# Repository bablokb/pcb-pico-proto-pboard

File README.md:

Protoyping Board for the Raspberry Pi Pico
==========================================

This is a small prototyping board for the Pico. Besides
the normal 2x20 through holes for the Pico, the PCB also
provides additional sockets for the connection of peripherals.

The idea of this board is to simplify software-development
for standard breakouts, because it provides sockets for
these components and thus no wiring is necessary.

Some supported components:

  - Mini-I2C-OLED
  - EYESPI (typically for SPI-displays)
  - 2x Grove (I2C0/UART0 and I2C1)
  - ESP-01S or Lilygo T-01 C3
  - passive buzzer
  - MAX98357A (I2S mono-amplifier)
  - button-breakout (3xbutton, 1xGND)
  - RTC-socket (for this PCB: <https://github.com/bablokb/pcb-pico-pcf8563.git>)
  - Adafruit TPL5110 power-switch breakout
  - SD-card socket (on-board)
  - JST-PH2 battery connector
  - JST-PH3 connector (ADC)

Note that some components share pins, so it is *not possible* to use
all components in parallel! See [pinout](./pins.md) for details.

Ready to use Gerber, BOM and POS files for JLCPCB are in the subdirectory
"production_files".

Schematic
---------

Layout
------

3D-Views
--------

License
-------

[![CC BY-SA 4.0][cc-by-sa-shield]][cc-by-sa]

This work is licensed under a
[Creative Commons Attribution-ShareAlike 4.0 International
License][cc-by-sa].

[![CC BY-SA 4.0][cc-by-sa-image]][cc-by-sa]

[cc-by-sa]: http://creativecommons.org/licenses/by-sa/4.0/
[cc-by-sa-image]: https://licensebuttons.net/l/by-sa/4.0/88x31.png
[cc-by-sa-shield]:
https://img.shields.io/badge/License-CC%20BY--SA%204.0-lightgrey.svg

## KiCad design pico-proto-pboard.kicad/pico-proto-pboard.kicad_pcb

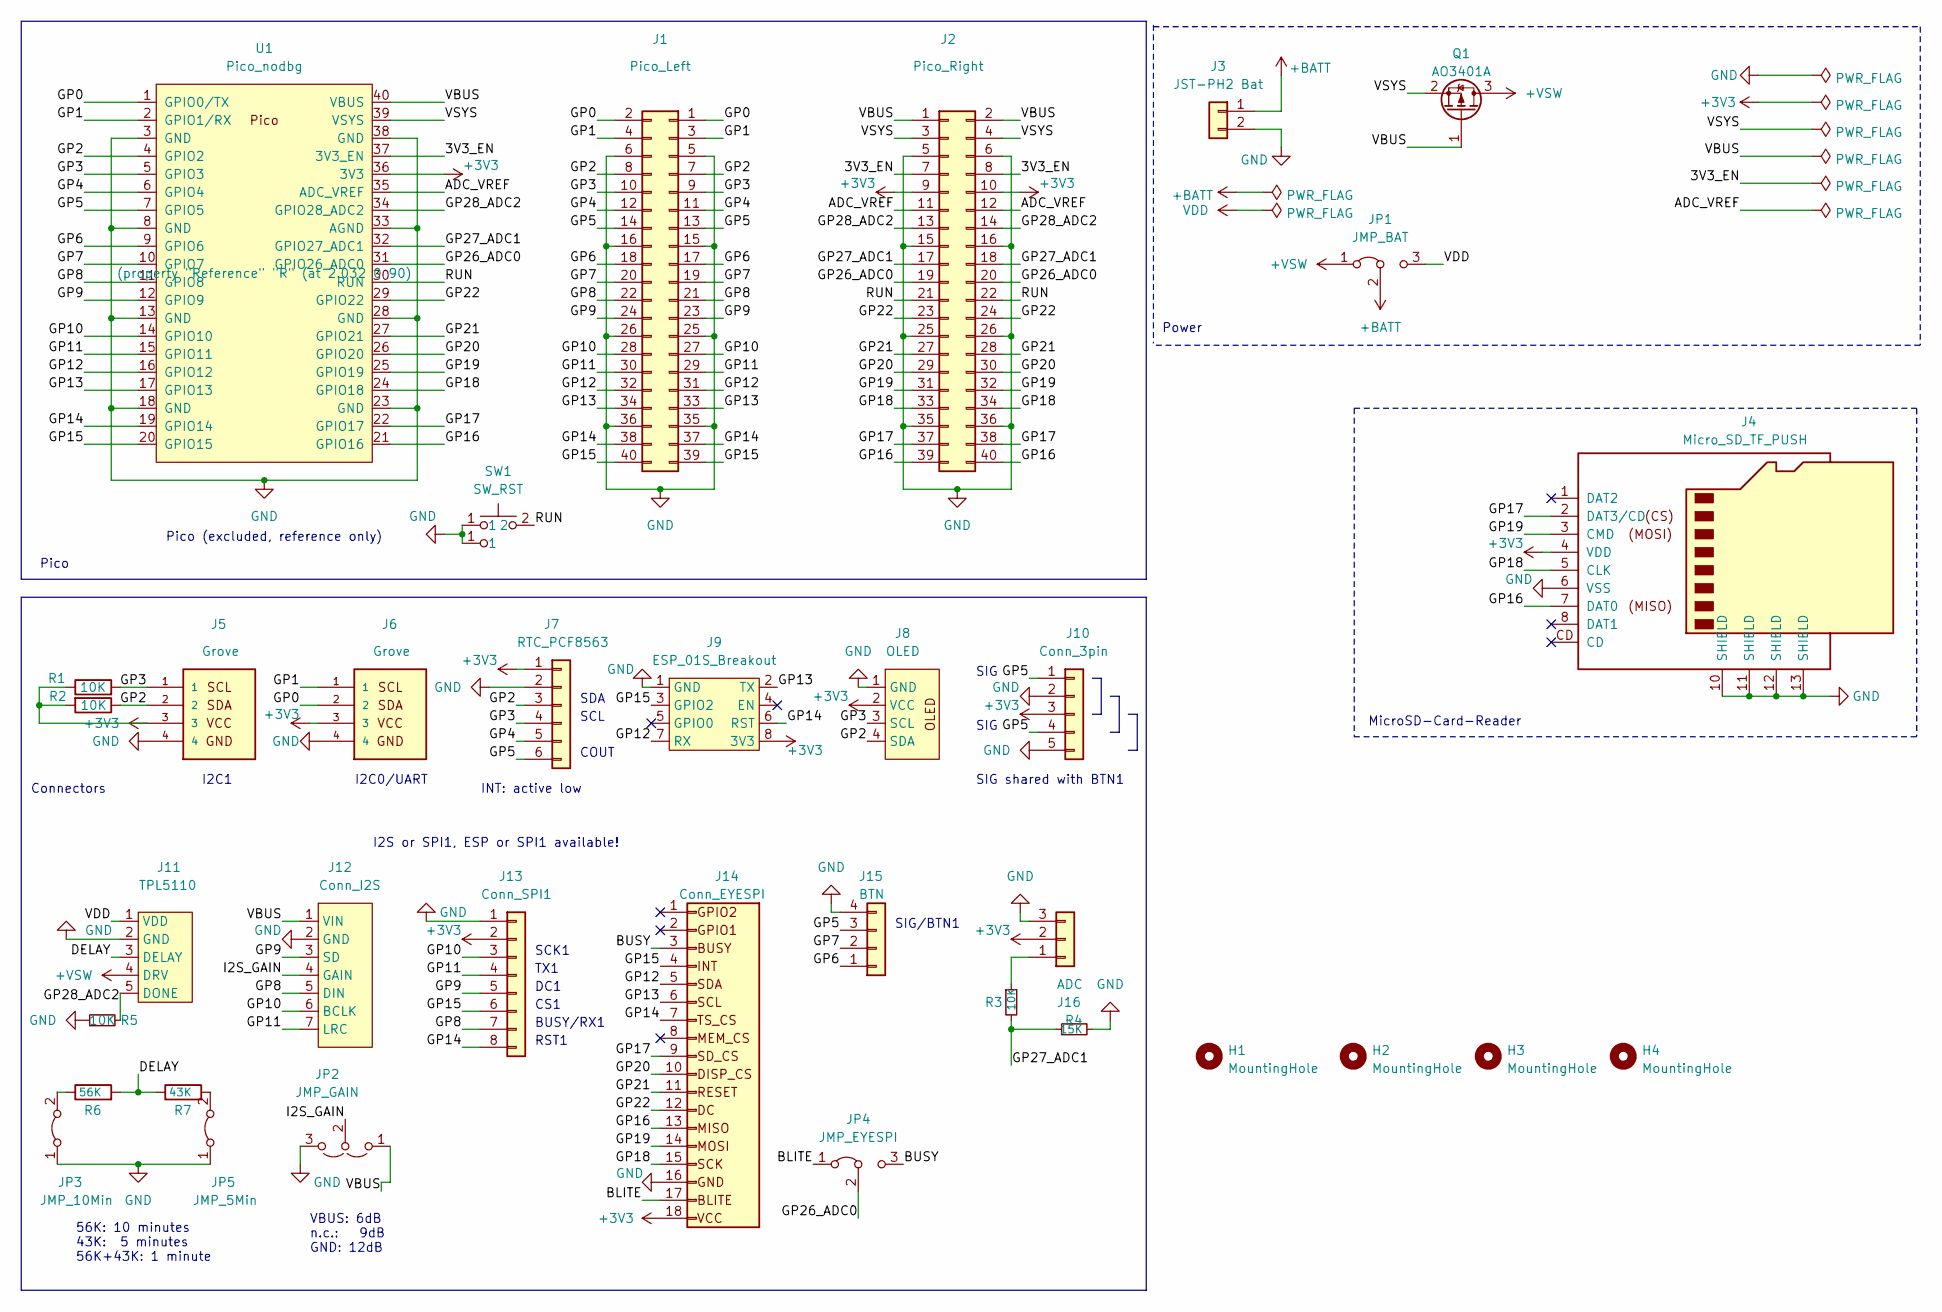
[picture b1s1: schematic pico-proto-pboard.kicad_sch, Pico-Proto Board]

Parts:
H1, H2, H3, H4: MountingHole; MountingHole_2.5mm
J1: Pico_Left; PinSocket_2x20_P2.54mm_Vertical
J2: Pico_Right; PinSocket_2x20_P2.54mm_Vertical
J3: JST-PH2 Bat; JST_PH_S2B-PH-SM4-TB_1x02-1MP_P2.00mm_Horizontal; LCSC C295747
J4: Micro_SD_TF_PUSH; TF-Push; LCSC C393941
J5, J6: Grove; grove_vertical
J7: RTC_PCF8563; PinSocket_1x06_P2.54mm_Vertical
J8: OLED; OLED_Display
J9: ESP_01S_Breakout
J10: Conn_3pin; PinSocket_1x05_P2.54mm_Vertical
J11: TPL5110; TPL5110_Breakout
J12: Conn_I2S; MAX98357A_Breakout
J13: Conn_SPI1; PinHeader_2x04_P2.54mm_Vertical
J14: Conn_EYESPI; G-Shell-FPC_1x18_P0.50mm_Horizontal; LCSC C21260844
J15: BTN; PinSocket_1x04_P2.54mm_Vertical
J16: ADC; JST_PH_S3B-PH-SM4-TB_1x03-1MP_P2.00mm_Horizontal
JP1: JMP_BAT; PinHeader_1x03_P2.54mm_Vertical
JP2: JMP_GAIN; PinHeader_1x03_P2.54mm_Vertical
JP3: JMP_10Min; SolderJumper-2_P1.3mm_Bridged_Pad1.0x1.5mm
JP4: JMP_EYESPI; SolderJumper-3_P1.3mm_Bridged12_Pad1.0x1.5mm
JP5: JMP_5Min; SolderJumper-2_P1.3mm_Bridged_Pad1.0x1.5mm
Q1: AO3401A; SOT-23; LCSC C15127
R1, R2, R3, R5: 10K; R_0402_1005Metric; LCSC C25744
R4: 15K; R_0402_1005Metric; LCSC C25756
R6: 56K; R_0402_1005Metric; LCSC C25796
R7: 43K; R_0603_1608Metric; LCSC C23172
SW1: SW_RST; SW_PUSH_SLIM_1x4
U1: Pico_nodbg; RPi_Pico_SMD_TH_nodbg; LCSC (property "Reference" "R" (at 2.032 0 9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

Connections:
+3V3: J2.9, J2.10, J4.4 (VDD), J5.3, J6.3, J7.1, J8.2 (VCC), J9.8 (3V3), J10.3, J13.2, J14.18, J16.2, R1.1, R2.2, U1.36 (3V3)
+BATT: J3.1, JP1.2 (C)
+VSW: J11.4 (DRV), JP1.1 (A), Q1.3 (D)
/3V3_EN: J2.7, J2.8, U1.37 (3V3_EN)
/ADC_VREF: J2.11, J2.12, U1.35 (ADC_VREF)
/BLITE: J14.17, JP4.1 (A)
/BUSY: J14.3, JP4.3 (B)
/DELAY: J11.3 (DELAY), R6.2, R7.1
/GP0: J1.1, J1.2, J6.2, U1.1 (GPIO0/TX)
/GP1: J1.3, J1.4, J6.1, U1.2 (GPIO1/RX)
/GP2: J1.7, J1.8, J5.2, J7.3, J8.4 (SDA), R2.1, U1.4 (GPIO2)
/GP3: J1.9, J1.10, J5.1, J7.4, J8.3 (SCL), R1.2, U1.5 (GPIO3)
/GP4: J1.11, J1.12, J7.5, U1.6 (GPIO4)
/GP5: J1.13, J1.14, J7.6, J10.1, J10.4, J15.3, U1.7 (GPIO5)
/GP6: J1.17, J1.18, J15.1, U1.9 (GPIO6)
/GP7: J1.19, J1.20, J15.2, U1.10 (GPIO7)
/GP8: J1.21, J1.22, J12.5 (DIN), J13.7, U1.11 (GPIO8)
/GP9: J1.23, J1.24, J12.3 (SD), J13.5, U1.12 (GPIO9)
/GP10: J1.27, J1.28, J12.6 (BCLK), J13.3, U1.14 (GPIO10)
/GP11: J1.29, J1.30, J12.7 (LRC), J13.4, U1.15 (GPIO11)
/GP12: J1.31, J1.32, J9.7 (RX), J14.5, U1.16 (GPIO12)
/GP13: J1.33, J1.34, J9.2 (TX), J14.6, U1.17 (GPIO13)
/GP14: J1.37, J1.38, J9.6 (RST), J13.8, J14.7, U1.19 (GPIO14)
/GP15: J1.39, J1.40, J9.3 (GPIO2), J13.6, J14.4, U1.20 (GPIO15)
/GP16: J2.39, J2.40, J4.7 (DAT0), J14.13, U1.21 (GPIO16)
/GP17: J2.37, J2.38, J4.2 (DAT3/CD), J14.9, U1.22 (GPIO17)
/GP18: J2.33, J2.34, J4.5 (CLK), J14.15, U1.24 (GPIO18)
/GP19: J2.31, J2.32, J4.3 (CMD), J14.14, U1.25 (GPIO19)
/GP20: J2.29, J2.30, J14.10, U1.26 (GPIO20)
/GP21: J2.27, J2.28, J14.11, U1.27 (GPIO21)
/GP22: J2.23, J2.24, J14.12, U1.29 (GPIO22)
/GP26_ADC0: J2.19, J2.20, JP4.2 (C), U1.31 (GPIO26_ADC0)
/GP27_ADC1: J2.17, J2.18, R3.2, R4.1, U1.32 (GPIO27_ADC1)
/GP28_ADC2: J2.13, J2.14, J11.5 (DONE), R5.2, U1.34 (GPIO28_ADC2)
/I2S_GAIN: J12.4 (GAIN), JP2.2 (C)
/RUN: J2.21, J2.22, SW1.2, U1.30 (RUN)
/VBUS: J2.1, J2.2, J12.1 (VIN), JP2.1 (A), Q1.1 (G), U1.40 (VBUS)
/VSYS: J2.3, J2.4, Q1.2 (S), U1.39 (VSYS)
GND: J1.5, J1.6, J1.15, J1.16, J1.25, J1.26, J1.35, J1.36, J2.5, J2.6, J2.15, J2.16, J2.25, J2.26, J2.35, J2.36, J3.2, J4.6 (VSS), J4.10 (SHIELD), J4.11 (SHIELD), J4.12 (SHIELD), J4.13 (SHIELD), J5.4, J6.4, J7.2, J8.1 (GND), J9.1 (GND), J10.2, J10.5, J11.2 (GND), J12.2 (GND), J13.1, J14.16, J15.4, J16.3, JP2.3 (B), JP3.1 (A), JP5.1 (A), R4.2, R5.1, SW1.1, U1.3 (GND), U1.8 (GND), U1.13 (GND), U1.18 (GND), U1.23 (GND), U1.28 (GND), U1.33 (AGND), U1.38 (GND)
unnamed: J16.1, R3.1
unnamed: JP3.2 (B), R6.1
unnamed: JP5.2 (B), R7.2
VDD: J11.1 (VDD), JP1.3 (B)

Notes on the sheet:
SIG
TX1
56K: 10 minutes 43K: 5 minutes 56K+43K: 1 minute
SDA
Pico (excluded, reference only)
DC1
CS1
SCK1
I2S or SPI1, ESP or SPI1 available!
INT: active low
Pico
SCL
Power
MicroSD-Card-Reader
SIG shared with BTN1
BUSY/RX1
SIG/BTN1
Connectors
RST1
VBUS: 6dB n.c.: 9dB GND: 12dB
I2C0/UART
I2C1
COUT

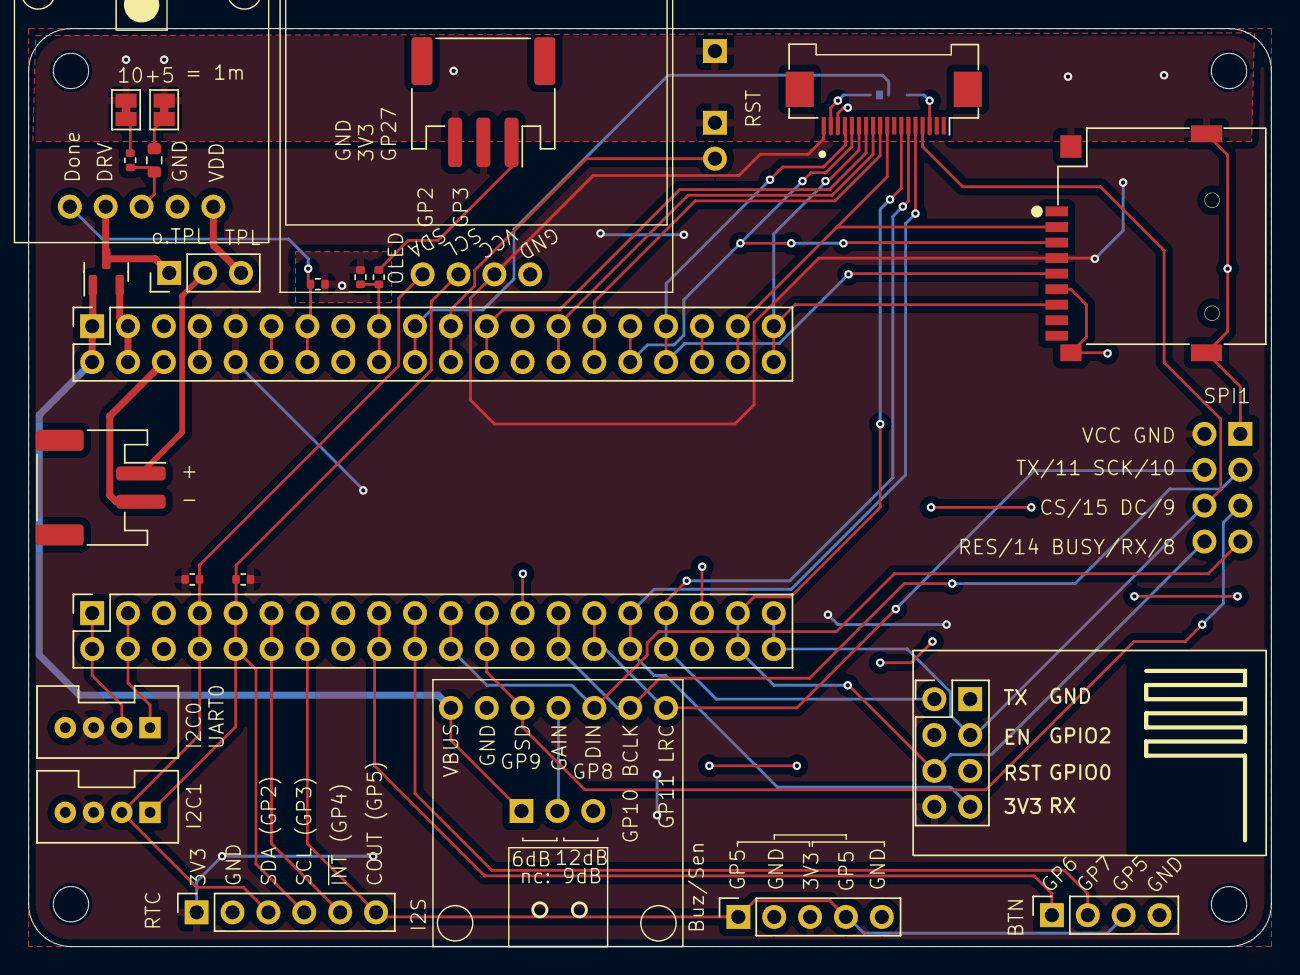
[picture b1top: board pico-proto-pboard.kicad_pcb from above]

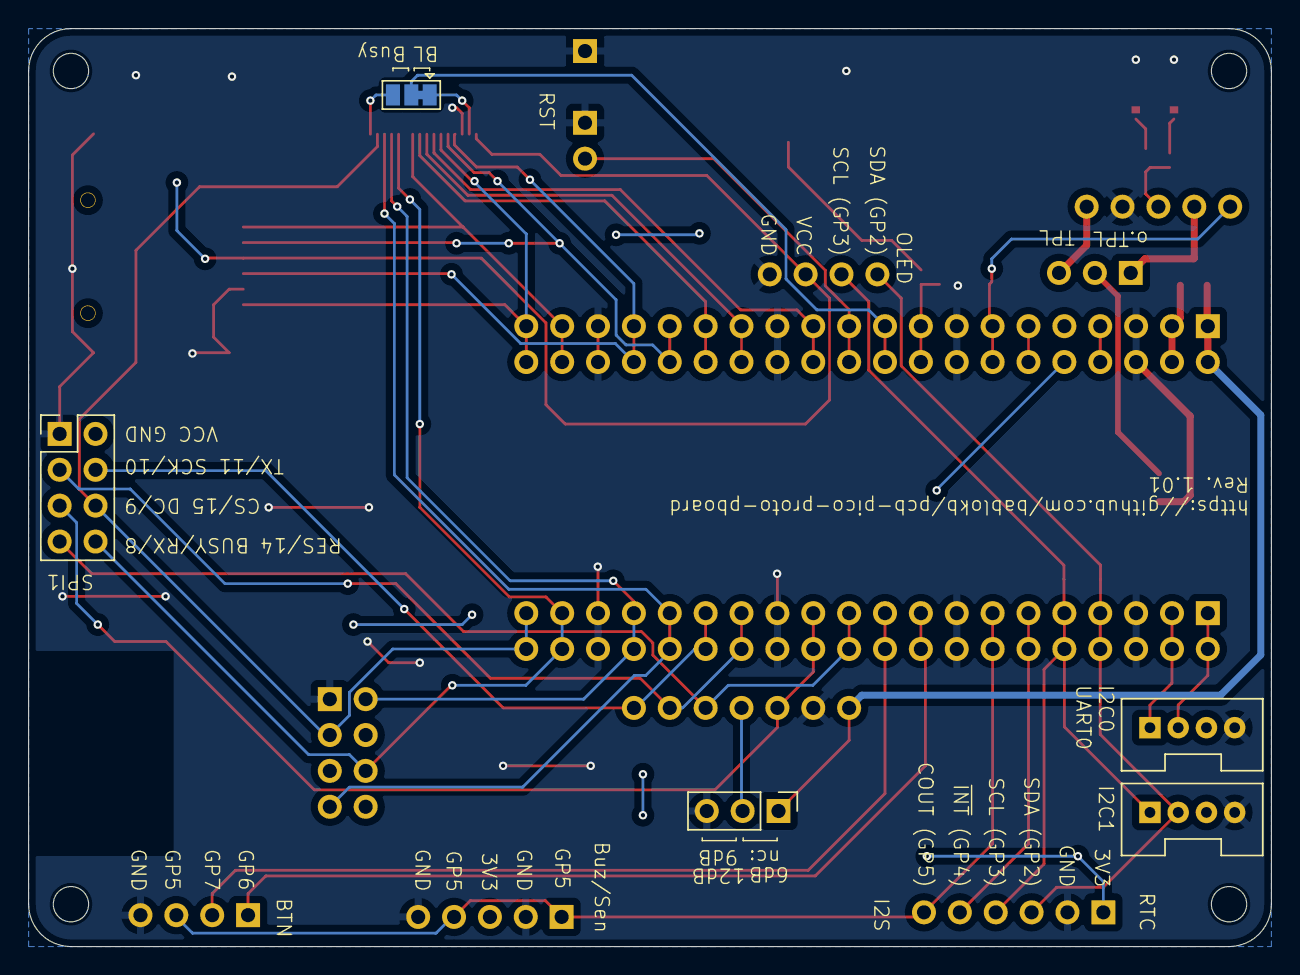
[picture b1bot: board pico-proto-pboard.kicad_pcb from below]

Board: 2 copper layers, 88.0 x 65.0 mm, 34 parts (3 on the bottom side), 43 nets.

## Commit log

2025-05-27 replace template with real content
2025-05-27 add note about shared pins and link to pins.md
2025-05-27 document jumper for backlight/busy
2025-07-01 added python files
2025-07-01 created support-library and show_time example
2025-07-01 added buzzer_music example
2025-07-02 add support for I2S-breakout incl. mute-pin
2025-07-02 added music-player example
2025-07-02 added example for TPL5110
2025-07-02 fix: wait_for_console(): add missing 'import time'
2025-07-02 eyespi_display(): implement default display
2025-07-02 use default EYESPI-display
2025-07-14 added ESP32 co-processor example
2025-07-15 added sensor-button example
2025-07-17 added BME280 example
2025-07-17 add some more chars
2025-07-17 fix problems with deep-sleep
2025-08-05 uart0(): add baudrate as parameter
2025-08-05 added DFPlayer example
2025-08-08 added 'N' and 'S' to position map
2025-08-08 added RTC-alarm example
